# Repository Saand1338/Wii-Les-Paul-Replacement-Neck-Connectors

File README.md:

# Wii Les Paul Replacement Neck Connectors

## License
This project is licensed under the **Creative Commons Attribution-ShareAlike 4.0 International License (CC BY-SA 4.0)**.
You’re free to modify and redistribute these files - including for commercial use - as long as you provide attribution and distribute any derivative works under the same license.

---

## Overview
This repository provides KiCad project files and Gerber exports for replacement circuit boards that make up the neck connection on the **Wii Les Paul (LP) Controller**.

The connector assembly consists of two PCBs:
- **Pogo Board** - located in the main controller body, fitted with pogo pins.
- **Interface Board** - located in the neck, containing the contact pads.

Together, they enable the detachable electrical connection between the neck and the body.
These PCBS are designed to use the Same Sky CPG-01-TH-B pogo pins, which have an operational range of 9.20-11.00 mm.
This range aligns with the \~10.6 mm engagement distance of the original Wii LP connector.

---

## Versions

### **6-Pin Version (Drop-in Replacement)**
A direct replacement for the original connector PCBs.
- Backwards compatible with the stock controller.
- Either board (pogo or interface) can be swapped independently.
- Intended for repairs or restorations using existing wiring.

**Pogo Board:**

**Interface Board:**

---

### **9-Pin Version (Expanded Functionality)**
A modernized redesign that adds three additional pins for RGB LED support.
- **Not backwards compatible** with the original connector boards.
- Designed for setups using addressable RGB LEDs such as the APA102.
- The GND connection is shared between the LEDs and fret circuits in this version.

**Pogo Board:**

**Interface Board:**

---

## Assembly Instructions

The pogo pins are intended to be soldered from the rear of the circuit board.
To assist with alignment, this repository includes optional STL files for support fixtures.
If a printed fixture is not available, an unpopulated PCB can serve as an alignment jig.

**Assembly steps:**

1. Place the alignment fixture upside down
2. Insert all pogo pins plunger-side down.
3. Position the pogo board onto the pins. If using a fixture, press it firmly into place.
4. Solder each pin from the rear of the board, taking care to avoid bridging adjacent pads.
5. Optionally leave the alignment fixture attached as a mechanical support, though it is not required for normal operation.

---

## Included Files

- KiCad project directories (`.kicad_pcb`, `.kicad_sch`, etc.)
- Exported Gerber files ready for PCB fabrication
- STL files for pogo-pin alignment fixtures

---

## Notes

- All PCB layouts were designed in millimeter **(mm)** units.
- These designs require the Same Sky CPG-01-TH-B pogo pins (range = 9.20 mm - 11.10 mm).
- Verify pogo pin height and compression range before soldering to ensure reliable contact.

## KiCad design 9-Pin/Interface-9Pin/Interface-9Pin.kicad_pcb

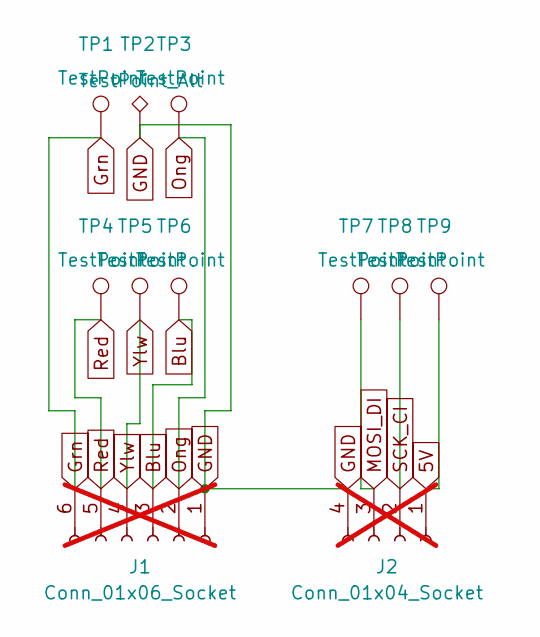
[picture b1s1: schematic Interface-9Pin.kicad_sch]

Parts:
J1: Conn_01x06_Socket; PinSocket_1x06_P2.54mm_Vertical; not fitted
J2: Conn_01x04_Socket; PinSocket_1x04_P2.54mm_Vertical; not fitted
TP1, TP3, TP4, TP5, TP6, TP7, TP8, TP9: TestPoint; TestPoint_Pad_D2.75mm
TP2: TestPoint_Alt; TestPoint_Pad_D2.75mm

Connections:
5V: J2.1, TP9.1
Blu: J1.3, TP6.1
GND: J1.1, J2.4, TP2.1
Grn: J1.6, TP1.1
MOSI_DI: J2.3, TP7.1
Ong: J1.2, TP3.1
Red: J1.5, TP4.1
SCK_CI: J2.2, TP8.1
Ylw: J1.4, TP5.1

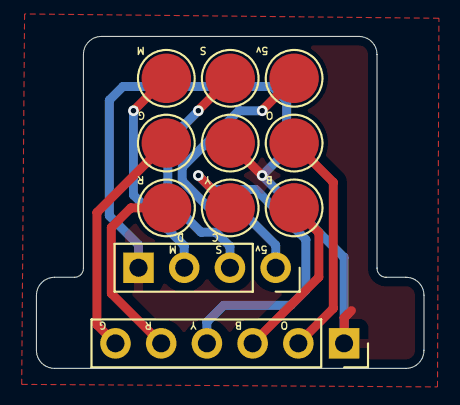
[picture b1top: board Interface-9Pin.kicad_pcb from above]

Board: 2 copper layers, 21.5 x 18.4 mm, 11 parts (0 on the bottom side), 9 nets.

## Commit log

2025-10-31 Initial commit of files, including licence, readme and .git files
